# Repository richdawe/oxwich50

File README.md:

# Oxwich50

The Oxwich50 keyboard is a 40-50% keyboard that can be mounted in a 60% traymount case, using the GH60 mounting points.

It was inspired by the many unibody split keyboards that I saw in the [Keyboard Builders Digest newsletter](https://kbd.news/). A lot of those keyboards had 30-36 keys, which seemed like too few for me. I wondered what a 60% keyboard would be like if you removed some keys, added an arrow cluster, and split the halves a bit, for a _potentially_ more comfortable typing position.

The PCB and plate were designed and made for me by [Mechboards Ltd](https://mechboards.co.uk/) in the UK.

Please see also my [keymap](https://github.com/richdawe/qmk_firmware/blob/master/keyboards/oxwich50/keymaps/richdawe/keymap.c) and the [QMK support](https://github.com/richdawe/qmk_firmware/tree/master/keyboards/oxwich50), both in my fork of the QMK firmware.

The keyboard is named after [Oxwich](https://en.wikipedia.org/wiki/Oxwich), which is a village on the Gower, near Swansea in Wales, UK.

# TODOs

 - [ ] Licence for h/w
 - [ ] Add photos
 - [ ] List of limitations with v1
   - [ ] plate hole in wrong place, stab screw conflict with 60% case post, maybe unnecessary holes? in the plate for 60% cases I use
   - [ ] also need to clip one of the plastic legs on a switch going in the RHS enter position - this is on the RHS, row above bottom one; was this with 5-pin switches?
   - [ ] holes for stabs are quite tight, could make them wider - also would they fit more stabs if they were taller?
 - [ ] Make the PCB compatible with o-ring mounting in a Bakeneko60 case
 - [ ] Other improvements? E.g.: Expose Pico debug connector for debugging QMK with the Rasbperry Pi debug peripheral?

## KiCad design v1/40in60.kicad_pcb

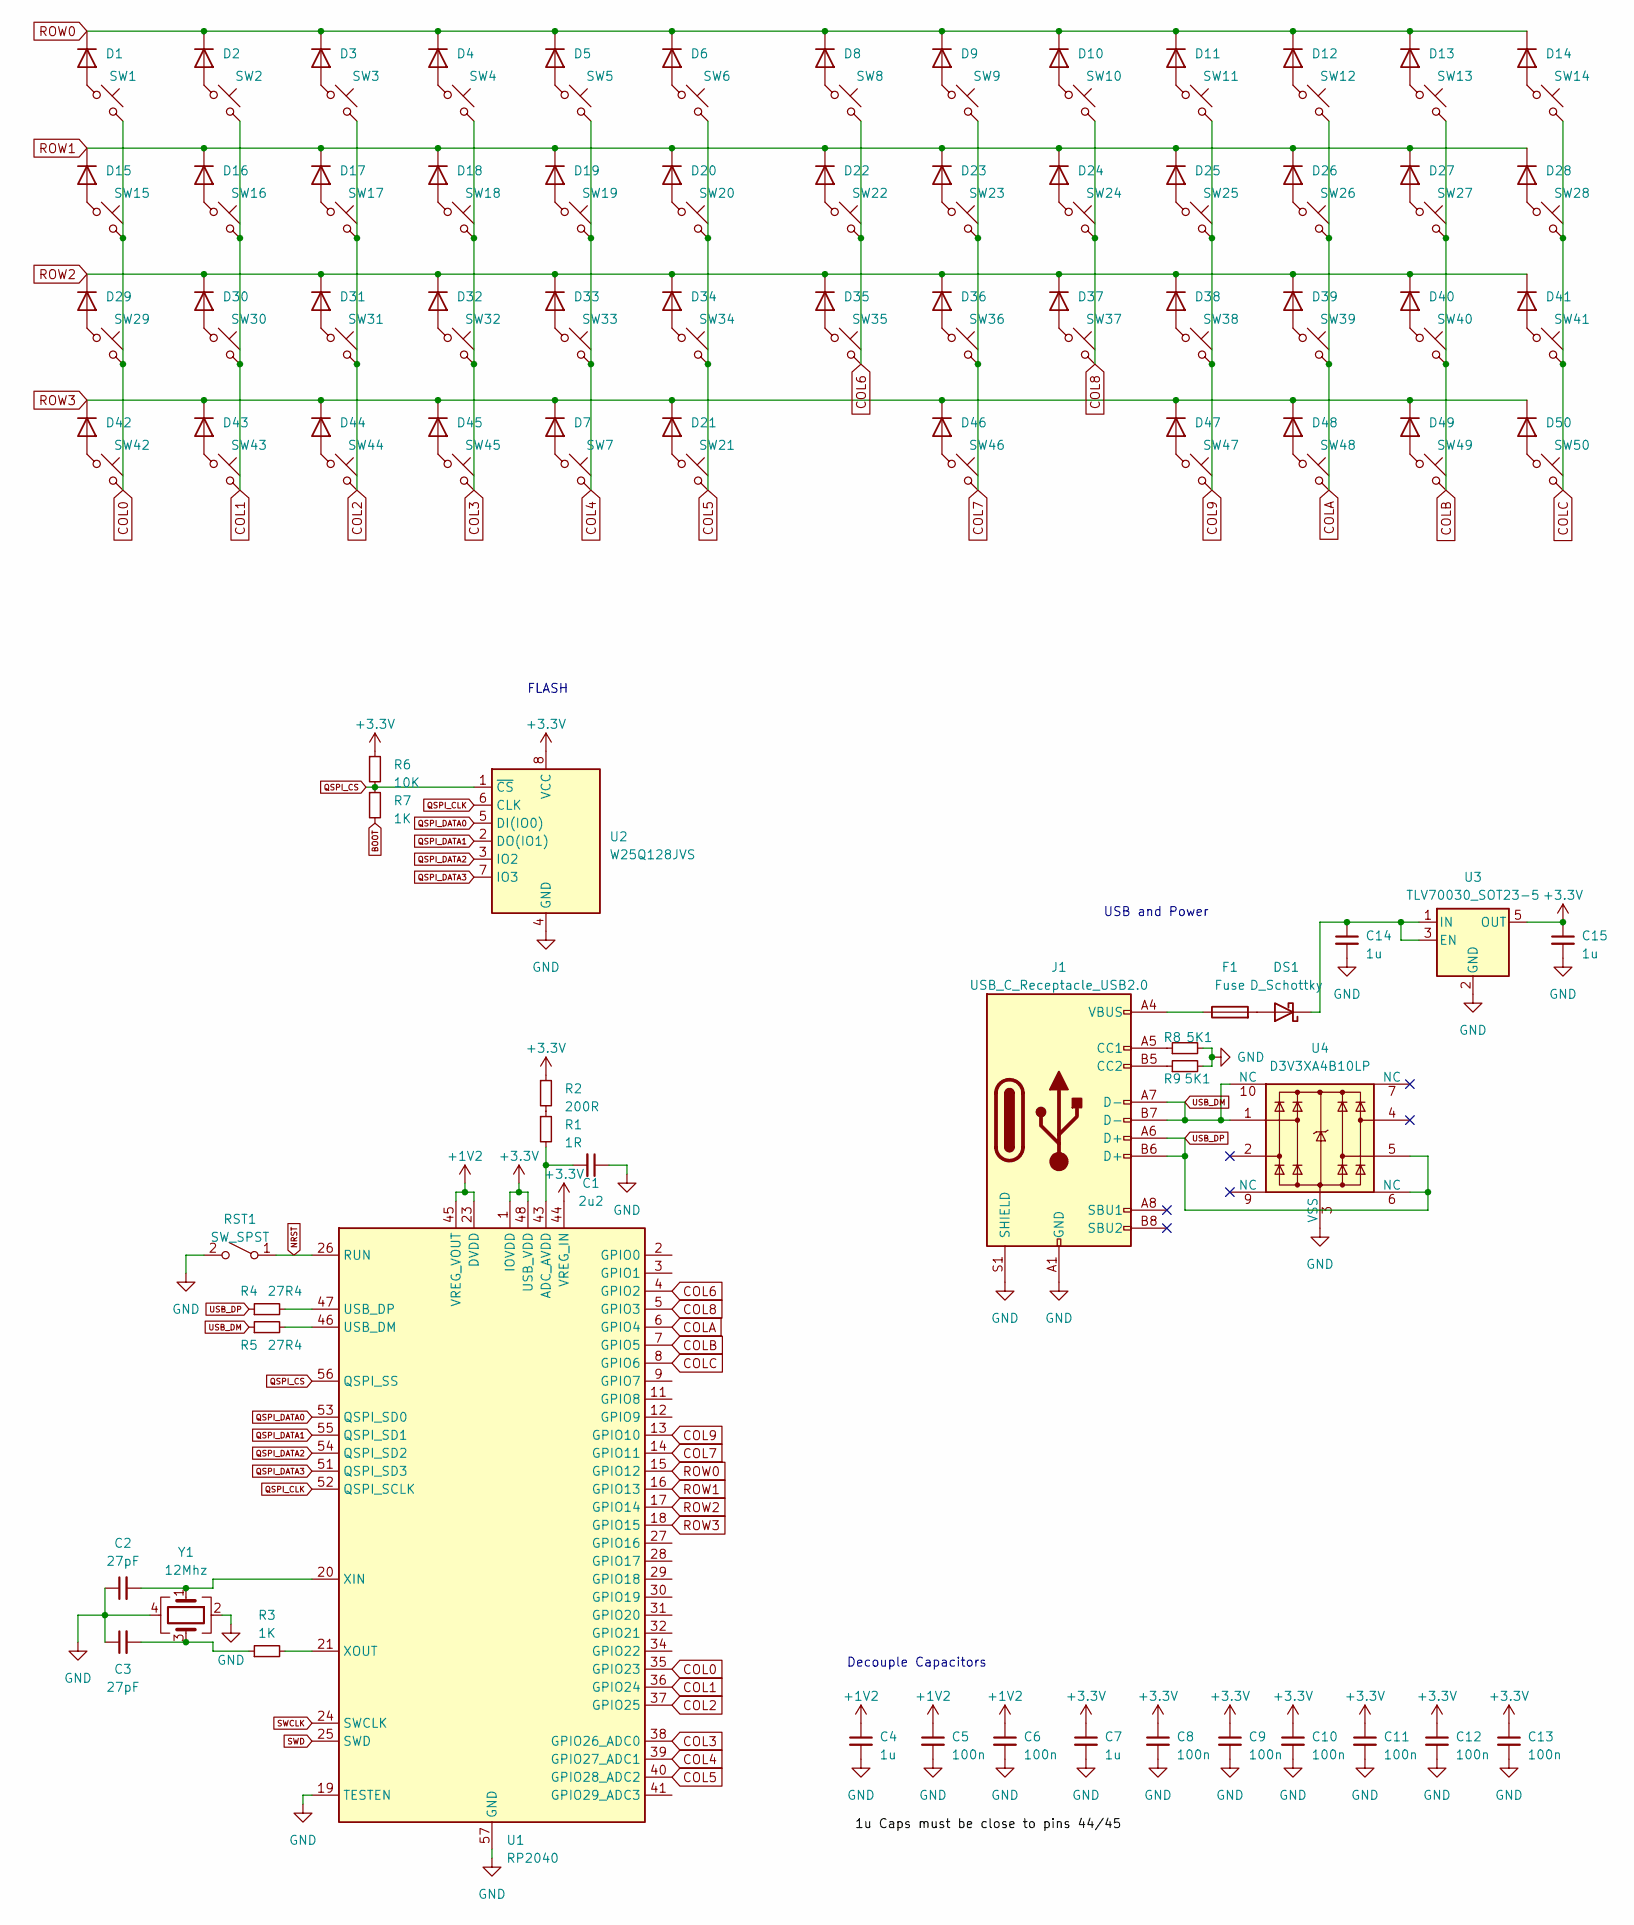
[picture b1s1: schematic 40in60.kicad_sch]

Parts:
C1: 2u2; C_0402_1005Metric
C2, C3: 27pF; C_0402_1005Metric
C4, C7, C14, C15: 1u; C_0402_1005Metric
C5, C6, C8, C9, C10, C11, C12, C13: 100n; C_0402_1005Metric
D1, D2, D3, D4, D5, D6, D7, D8, D9, D10, D11, D12, D13, D14, D15, D16, D17, D18, D19, D20, D21, D22, D23, D24, D25, D26, D27, D28, D29, D30, D31, D32, D33, D34, D35, D36, D37, D38, D39, D40, D41, D42, D43, D44, D45, D46, D47, D48, D49, D50: 1N4148W; D_SOD-123
DS1: D_Schottky; D_SOD-123
F1: Fuse; R_0805_2012Metric_Pad1.20x1.40mm_HandSolder
J1: USB_C_Receptacle_USB2.0; USB_C_Receptacle_HRO_TYPE-C-31-M-12
R1: 1R; R_0402_1005Metric
R2: 200R; R_0402_1005Metric
R3, R7: 1K; R_0402_1005Metric
R4, R5: 27R4; R_0402_1005Metric
R6: 10K; R_0402_1005Metric
R8, R9: 5K1; R_0402_1005Metric
RST1: SW_SPST; SW_SPST_TL3342
SW1, SW2, SW3, SW4, SW5, SW6, SW7, SW8, SW9, SW10, SW11, SW12, SW13, SW15, SW16, SW17, SW18, SW19, SW20, SW21, SW22, SW23, SW24, SW25, SW26, SW27, SW28, SW30, SW31, SW32, SW33, SW34, SW35, SW36, SW37, SW38, SW39, SW40, SW41, SW48, SW49, SW50: SW_Push_45deg; SW_Hotswap_Kailh_MX_1.00u
SW14, SW47: SW_Push_45deg; SW_Hotswap_Kailh_MX_1.50u
SW29: SW_Push_45deg; SW_Hotswap_Kailh_MX_1.75u
SW42, SW43, SW44: SW_Push_45deg; SW_Hotswap_Kailh_MX_1.25u
SW45: SW_Push_45deg; SW_Hotswap_Kailh_MX_2.75u
SW46: SW_Push_45deg; SW_Hotswap_Kailh_MX_2.25u
U1: RP2040; QFN-56-1EP_7x7mm_P0.4mm_EP3.2x3.2mm
U2: W25Q128JVS; SOIC-8_5.23x5.23mm_P1.27mm
U3: TLV70030_SOT23-5; SOT-23-5
U4: D3V3XA4B10LP; Diodes_UDFN-10_1.0x2.5mm_P0.5mm
Y1: 12Mhz; Crystal_SMD_2520-4Pin_2.5x2.0mm

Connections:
+1V2: C4.1, C5.1, C6.1, U1.23 (DVDD), U1.45 (VREG_VOUT), U1.50 (DVDD)
+3.3V: C7.1, C8.1, C9.1, C10.1, C11.1, C12.1, C13.1, C15.1, R2.1, R6.1, U1.1 (IOVDD), U1.10 (IOVDD), U1.22 (IOVDD), U1.33 (IOVDD), U1.42 (IOVDD), U1.44 (VREG_IN), U1.48 (USB_VDD), U1.49 (IOVDD), U2.8 (VCC), U3.5 (OUT)
BOOT: R7.2
COL0: SW1.2, SW15.2, SW29.2, SW42.2, U1.35 (GPIO23)
COL1: SW2.2, SW16.2, SW30.2, SW43.2, U1.36 (GPIO24)
COL2: SW3.2, SW17.2, SW31.2, SW44.2, U1.37 (GPIO25)
COL3: SW4.2, SW18.2, SW32.2, SW45.2, U1.38 (GPIO26_ADC0)
COL4: SW5.2, SW7.2, SW19.2, SW33.2, U1.39 (GPIO27_ADC1)
COL5: SW6.2, SW20.2, SW21.2, SW34.2, U1.40 (GPIO28_ADC2)
COL6: SW8.2, SW22.2, SW35.2, U1.4 (GPIO2)
COL7: SW9.2, SW23.2, SW36.2, SW46.2, U1.14 (GPIO11)
COL8: SW10.2, SW24.2, SW37.2, U1.5 (GPIO3)
COL9: SW11.2, SW25.2, SW38.2, SW47.2, U1.13 (GPIO10)
COLA: SW12.2, SW26.2, SW39.2, SW48.2, U1.6 (GPIO4)
COLB: SW13.2, SW27.2, SW40.2, SW49.2, U1.7 (GPIO5)
COLC: SW14.2, SW28.2, SW41.2, SW50.2, U1.8 (GPIO6)
GND: C1.1, C2.1, C3.1, C4.2, C5.2, C6.2, C7.2, C8.2, C9.2, C10.2, C11.2, C12.2, C13.2, C14.2, C15.2, J1.A1 (GND), J1.A12 (GND), J1.B1 (GND), J1.B12 (GND), J1.S1 (SHIELD), R8.2, R9.2, RST1.2 (B), U1.19 (TESTEN), U1.57 (GND), U2.4 (GND), U3.2 (GND), U4.3 (VSS), U4.8 (VSS), Y1.2, Y1.4
NRST: RST1.1 (A), U1.26 (RUN)
unnamed: C3.2, R3.1, Y1.3
unnamed: D1.2 (A), SW1.1
unnamed: D2.2 (A), SW2.1
unnamed: D3.2 (A), SW3.1
unnamed: D4.2 (A), SW4.1
unnamed: D5.2 (A), SW5.1
unnamed: D6.2 (A), SW6.1
unnamed: D7.2 (A), SW7.1
unnamed: D8.2 (A), SW8.1
unnamed: D9.2 (A), SW9.1
unnamed: D10.2 (A), SW10.1
unnamed: D11.2 (A), SW11.1
unnamed: D12.2 (A), SW12.1
unnamed: D13.2 (A), SW13.1
unnamed: D14.2 (A), SW14.1
unnamed: D15.2 (A), SW15.1
unnamed: D16.2 (A), SW16.1
unnamed: D17.2 (A), SW17.1
unnamed: D18.2 (A), SW18.1
unnamed: D19.2 (A), SW19.1
unnamed: D20.2 (A), SW20.1
unnamed: D21.2 (A), SW21.1
unnamed: D22.2 (A), SW22.1
unnamed: D23.2 (A), SW23.1
unnamed: D24.2 (A), SW24.1
unnamed: D25.2 (A), SW25.1
unnamed: D26.2 (A), SW26.1
unnamed: D27.2 (A), SW27.1
unnamed: D28.2 (A), SW28.1
unnamed: D29.2 (A), SW29.1
unnamed: D30.2 (A), SW30.1
unnamed: D31.2 (A), SW31.1
unnamed: D32.2 (A), SW32.1
unnamed: D33.2 (A), SW33.1
unnamed: D34.2 (A), SW34.1
unnamed: D35.2 (A), SW35.1
unnamed: D36.2 (A), SW36.1
unnamed: D37.2 (A), SW37.1
unnamed: D38.2 (A), SW38.1
unnamed: D39.2 (A), SW39.1
unnamed: D40.2 (A), SW40.1
unnamed: D41.2 (A), SW41.1
unnamed: D42.2 (A), SW42.1
unnamed: D43.2 (A), SW43.1
unnamed: D44.2 (A), SW44.1
unnamed: D45.2 (A), SW45.1
unnamed: D46.2 (A), SW46.1
unnamed: D47.2 (A), SW47.1
unnamed: D48.2 (A), SW48.1
unnamed: D49.2 (A), SW49.1
unnamed: D50.2 (A), SW50.1
unnamed: DS1.2 (A), F1.2
unnamed: C14.1, DS1.1 (K), U3.1 (IN), U3.3 (EN)
unnamed: F1.1, J1.A4 (VBUS), J1.A9 (VBUS), J1.B4 (VBUS), J1.B9 (VBUS)
unnamed: J1.A5 (CC1), R8.1
unnamed: J1.B5 (CC2), R9.1
unnamed: R1.1, R2.2
unnamed: C1.2, R1.2, U1.43 (ADC_AVDD)
unnamed: R5.2, U1.46 (USB_DM)
unnamed: R4.2, U1.47 (USB_DP)
unnamed: C2.2, U1.20 (XIN), Y1.1
unnamed: R3.2, U1.21 (XOUT)
QSPI_CLK: U1.52 (QSPI_SCLK), U2.6 (CLK)
QSPI_CS: R6.2, R7.1, U1.56 (QSPI_SS), U2.1 (~CS)
QSPI_DATA0: U1.53 (QSPI_SD0), U2.5 (DI(IO0))
QSPI_DATA1: U1.55 (QSPI_SD1), U2.2 (DO(IO1))
QSPI_DATA2: U1.54 (QSPI_SD2), U2.3 (IO2)
QSPI_DATA3: U1.51 (QSPI_SD3), U2.7 (IO3)
ROW0: D1.1 (K), D2.1 (K), D3.1 (K), D4.1 (K), D5.1 (K), D6.1 (K), D8.1 (K), D9.1 (K), D10.1 (K), D11.1 (K), D12.1 (K), D13.1 (K), D14.1 (K), U1.15 (GPIO12)
ROW1: D15.1 (K), D16.1 (K), D17.1 (K), D18.1 (K), D19.1 (K), D20.1 (K), D22.1 (K), D23.1 (K), D24.1 (K), D25.1 (K), D26.1 (K), D27.1 (K), D28.1 (K), U1.16 (GPIO13)
ROW2: D29.1 (K), D30.1 (K), D31.1 (K), D32.1 (K), D33.1 (K), D34.1 (K), D35.1 (K), D36.1 (K), D37.1 (K), D38.1 (K), D39.1 (K), D40.1 (K), D41.1 (K), U1.17 (GPIO14)
ROW3: D7.1 (K), D21.1 (K), D42.1 (K), D43.1 (K), D44.1 (K), D45.1 (K), D46.1 (K), D47.1 (K), D48.1 (K), D49.1 (K), D50.1 (K), U1.18 (GPIO15)
SWCLK: U1.24 (SWCLK)
SWD: U1.25 (SWD)
USB_DM: J1.A7 (D-), J1.B7 (D-), R5.1, U4.1, U4.10 (NC)
USB_DP: J1.A6 (D+), J1.B6 (D+), R4.1, U4.5, U4.6 (NC)

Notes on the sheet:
Decouple Capacitors
USB and Power
FLASH

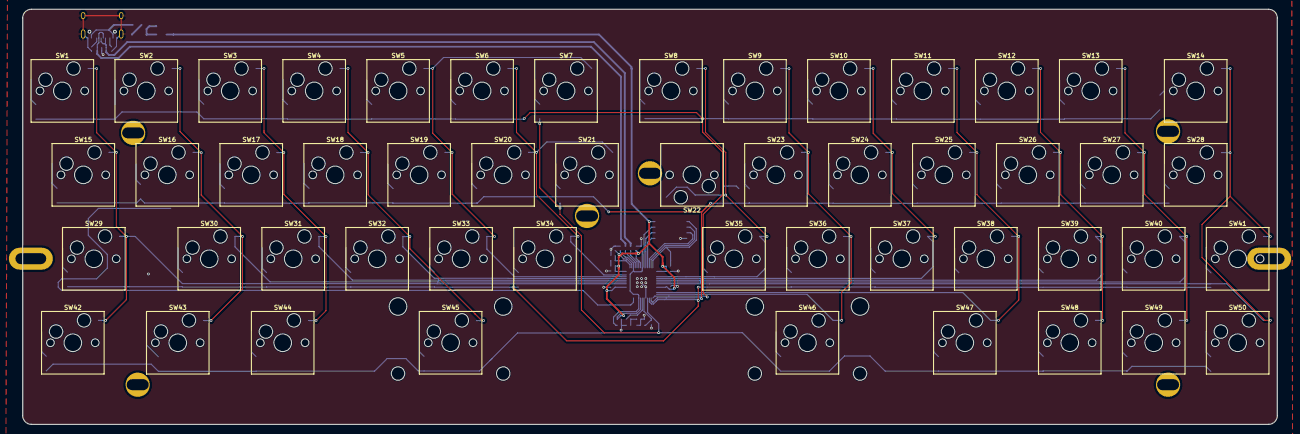
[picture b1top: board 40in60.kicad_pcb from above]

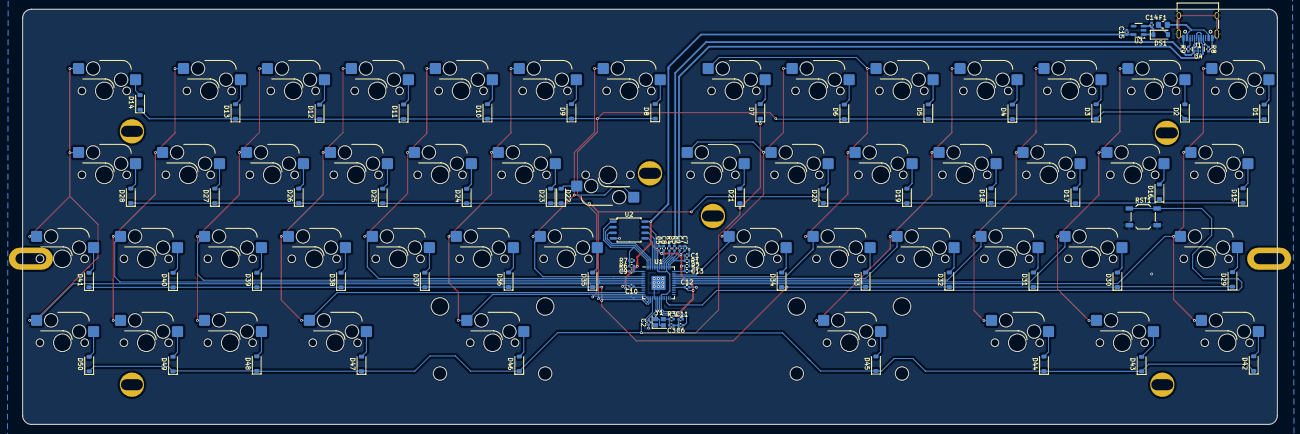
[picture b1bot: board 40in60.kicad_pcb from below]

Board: 2 copper layers, 284.7 x 94.2 mm, 133 parts (83 on the bottom side), 91 nets.

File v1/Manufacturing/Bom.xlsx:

Designator | Footprint | Quantity | Value | JLCPCB Part #
SW43,SW42,SW44,SW46,SW29,SW14,SW47,SW45,SW28,SW4,SW18,SW21,SW40,SW6,SW10,SW39,S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 | SW_Hotswap_Kailh_MX_1.00u | 50 | SW_Push_45deg | CPG151101S11
DS1 | D_SOD-123 | 1 | DSK34 SOD-123 | C41029
D7,D26,D49,D33,D17,D38,D2,D29,D31,D41,D40,D36,D11,D13,D39,D35,D24,D4,D43,D37,D4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 | D_SOD-123 | 50 | 1N4148W | C81598
U2 | SOIC-8_5.23x5.23mm_P1.27mm | 1 | W25Q128JVS | C97521
C14,C15,C4,C7 | C_0402_1005Metric | 4 | 1u | C52923
U3 | SOT-23-5 | 1 | TLV70030DDCR | C36463
R8,R9 | R_0402_1005Metric | 2 | 5K1 | C25905
R3,R7 | R_0402_1005Metric | 2 | 1K | C11702
C11,C9,C5,C6,C10,C12,C8,C13 | C_0402_1005Metric | 8 | 100n | C1525
U1 | QFN-56-1EP_7x7mm_P0.4mm_EP3.2x3.2mm | 1 | RP2040 | C2040
R5,R4 | R_0402_1005Metric | 2 | 27R4 | C284479
R2 | R_0402_1005Metric | 1 | 200R | C25087
RST1 | SW_SPST_TL3342 | 1 | SW_SPST_TL3342 | C2886897
C2,C3 | C_0402_1005Metric | 2 | 27pF | C86287
F1 | R_0805_2012Metric_Pad1.20x1.40mm_HandSolder | 1 | Fuse | C883108
Y1 | Crystal_SMD_2520-4Pin_2.5x2.0mm | 1 | 12Mhz, 10pf, 10ppm | C284154
C1 | C_0402_1005Metric | 1 | 2u2 | C12530
J1 | USB_C_Receptacle_HRO_TYPE-C-31-M-12 | 1 | USB_C_Receptacle_USB2.0 | C165948
R6 | R_0402_1005Metric | 1 | 10K | C25744
R1 | R_0402_1005Metric | 1 | 1R | C881121
U4 | Diodes_UDFN-10_1.0x2.5mm_P0.5mm | 1 | D3V3XA4B10LP | C1980462

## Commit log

2024-06-08 Import PCB and plate design by Mechboards
2024-06-08 TODOs
2024-06-16 Keyboard Editor Layout JSON and PNG
2025-02-08 More TODOs
2025-10-30 Description
2025-10-30 QR code script
2025-11-02 Stabilser holes are also a bit tight
